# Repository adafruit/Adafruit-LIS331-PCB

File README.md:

## PCB files for the Adafruit LIS331 Family of High-g 3-Axis Accelerometers
### LIS331HH
<a href="http://www.adafruit.com/products/4626"><br/>
Click here to purchase one from the Adafruit shop</a>
### H3LIS331
<a href="http://www.adafruit.com/products/4627"><br/>
Click here to purchase one from the Adafruit shop</a>
### Links
PCB files for the Adafruit LIS331 Family of High-g 3-Axis Accelerometers. 

Format is EagleCAD schematic and board layout
* https://www.adafruit.com/product/4626
* https://www.adafruit.com/product/4627

### Description

Accelerometers are becoming fairly common, and their clear connection to movement makes them a particularly good choice for learning about sensors in a tangible way. It’s not hard to find an accelerometer that can measure accelerations up to 16g, but if you need an accelerometer that can measure even larger amounts of acceleration, your options narrow. The ICM20649 is a great sensor and can measure up to ±30g, but it also comes with a magnetometer that you may not need for your project.

Enter the LIS331 family of accelerometers from ST, including the H3LIS331 and LIS331HH. As their model numbers may suggest, the LIS331s are close cousins to the venerable LIS3DH accelerometer that is on every Circuit Playground, from the Circuit Playground Classic to the newest Circuit Playground Bluefruit. The LIS331s however can measure a wider range of acceleration values.

The LIS331HHis capable of measuring up to ±24g on each of its three axes for a total range of 48g! Should that not be enough for you the H3LIS331 will certainly have you covered. At the reasonable cost of some signal noise at lower “human level” accelerations, the H3’ can measure up to ±400g! The mind boggles at trying to think of what would need to measure that much acceleration. Perhaps you bought a surplus Sprint missile to start your own space program, or maybe you have an idea for a rocket sled based pizza delivery startup. The sky is the limit!

In addition to their substantial measurement capability, the LIS331s have built in and configurable high-pass and low-pass filters to adjust the readings to your application. Adjustable data rates also allow you to adjust how frequently to take measurements depending on your power budget, and SPI and I2C interfaces give them flexibility to allow them to be used in a range of applications.

The breakout for the  LIS331 family takes one of these little dynamos and puts it on a custom made PCB in the STEMMA QT form factor, making them easy to interface with. The STEMMA QT connectors on either side are compatible with the SparkFun Qwiic I2C connectors, allowing you to make solderless connections between your development board and the LIS331s, as well as being chained with a wide range of other sensors and accessories. We’ve of course broken out all the pins to standard headers and added a voltage regulator and level shifting so allow you to use it with either 3.3V or 5V systems such as the Metro M4 or Arduino Uno respectively.

Fancy as they are, breakouts alone won’t get you far, so we’ve written libraries for CircuitPython and Arduino along with example code to make them simple to use. The documentation for how to use the libraries as well as wiring diagrams on the following pages will show you how to use them to get you started.

### License

Adafruit invests time and resources providing this open source design, please support Adafruit and open-source hardware by purchasing products from [Adafruit](https://www.adafruit.com)!

Designed by Limor Fried/Ladyada for Adafruit Industries.

Creative Commons Attribution/Share-Alike, all text above must be included in any redistribution. 
See license.txt for additional details.

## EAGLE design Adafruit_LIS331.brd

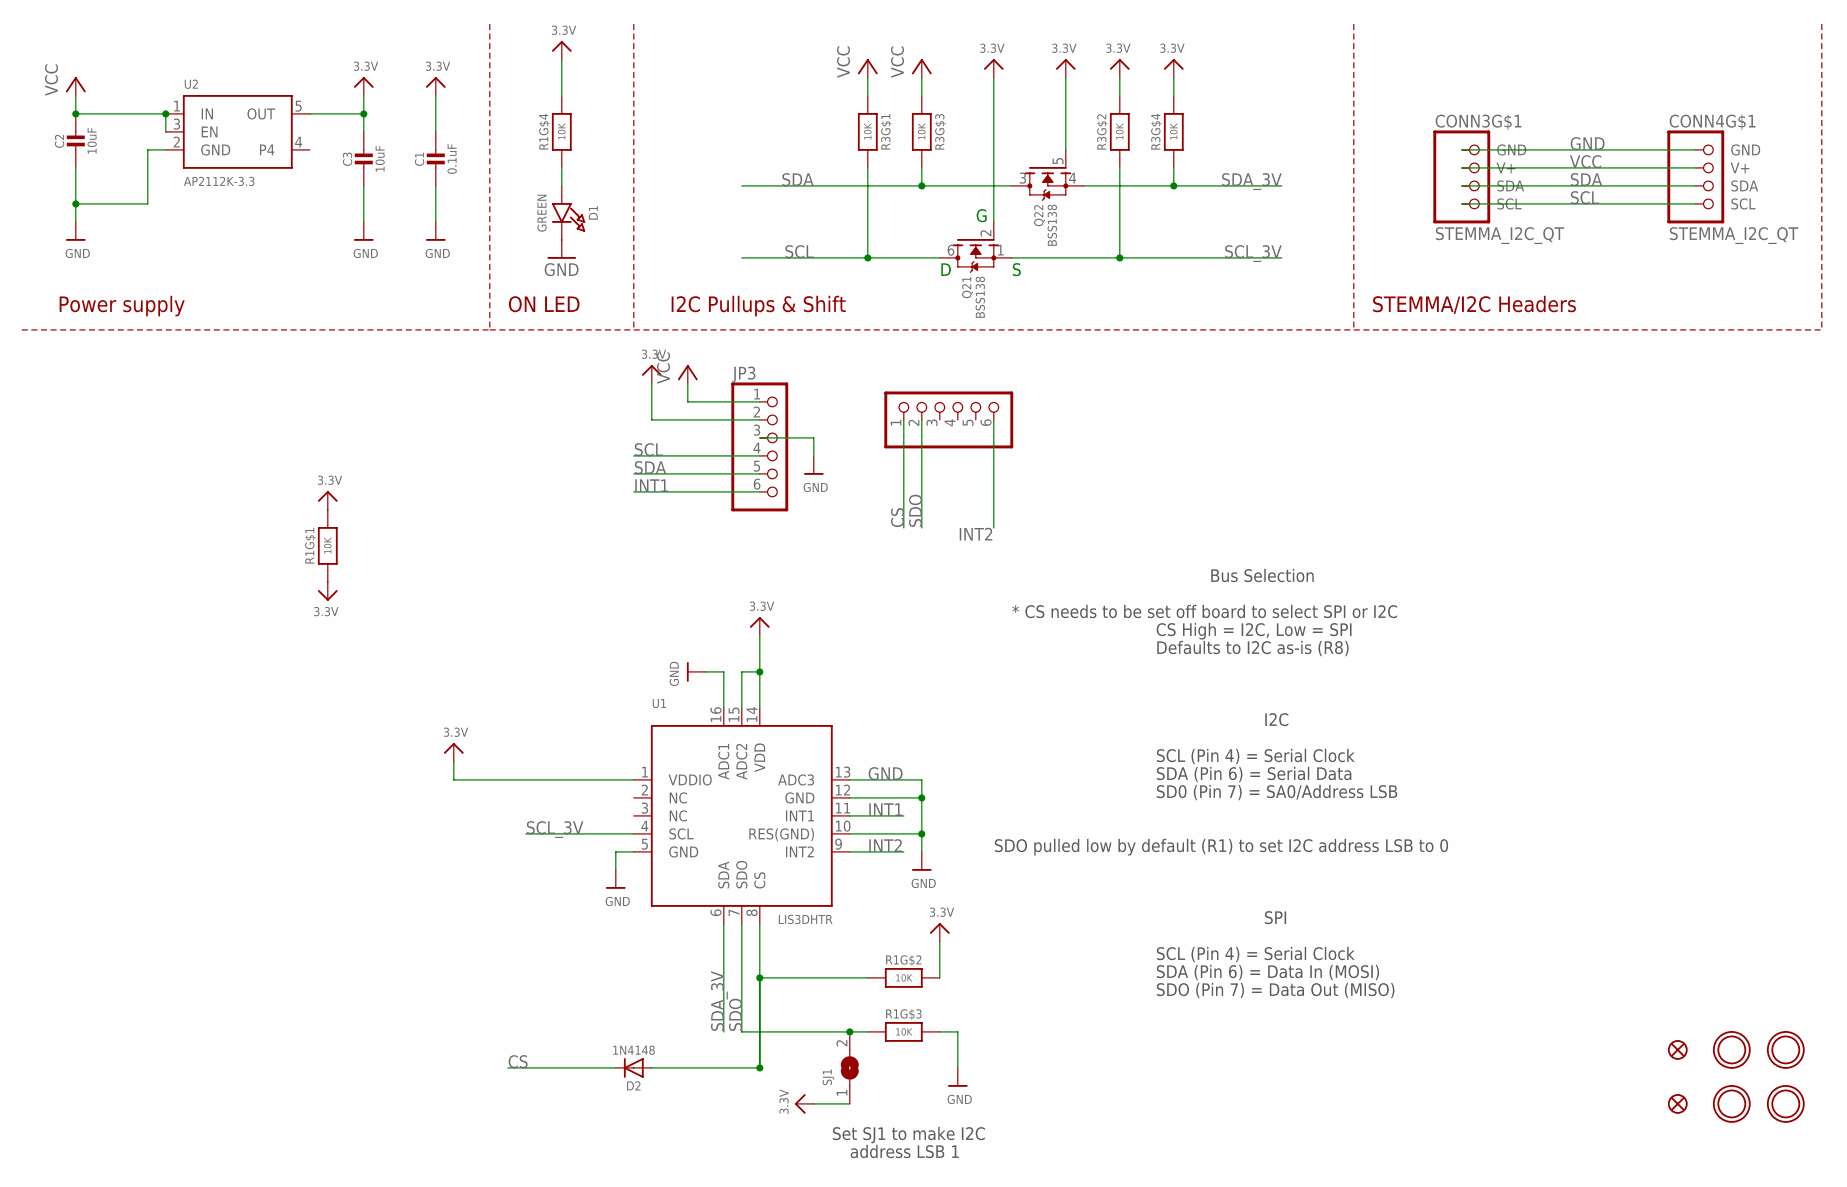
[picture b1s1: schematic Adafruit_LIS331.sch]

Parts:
C1: 0.1uF; 0603-NO
C2, C3: 10uF; 0805-NO
CONN3, CONN4: STEMMA_I2C_QT; JST_SH4
D1: GREEN; CHIPLED_0603_NOOUTLINE
D2: 1N4148; SOD-323
FID3, FID4: FIDUCIAL_1MM
JP2, JP3: HEADER-1X670MIL; 1X06_ROUND_70
Q2: BSS138; SOT363
R1, R3: 10K; RESPACK_4X0603
SJ1: SOLDERJUMPER; SOLDERJUMPER_ARROW_NOPASTE
U1: LIS3DHTR; LGA16_3X3MM
U2: AP2112K-3.3; SOT23-5
U$1, U$17, U$19, U$21: MOUNTINGHOLE2.5; MOUNTINGHOLE_2.5_PLATED

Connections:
3.3V: C1.1, C3.1, JP3.2, Q2.2 (G), Q2.5 (G), R1.1, R1.5 (2), R1.7 (2), R1.8 (2), R3.2 (1), R3.4 (1), SJ1.1, U1.1 (VDDIO), U1.14 (VDD), U1.15 (ADC2), U2.5 (OUT)
CS: D2.C, JP2.1
GND: C1.2, C2.2, C3.2, CONN3.1 (GND), CONN4.1 (GND), D1.C, JP3.3, R1.6 (2), U1.5 (GND), U1.10 (RES(GND)), U1.12 (GND), U1.13 (ADC3), U1.16 (ADC1), U2.2 (GND)
INT1: JP3.6, U1.11 (INT1)
INT2: JP2.6, U1.9 (INT2)
unnamed: D1.A, R1.4 (1)
unnamed: D2.A, R1.2 (1), U1.8 (CS)
SCL: CONN3.4 (SCL), CONN4.4 (SCL), JP3.4, Q2.6 (D), R3.8 (2)
SCL_3V: Q2.1 (S), R3.7 (2), U1.4 (SCL)
SDA: CONN3.3 (SDA), CONN4.3 (SDA), JP3.5, Q2.3 (D), R3.6 (2)
SDA_3V: Q2.4 (S), R3.5 (2), U1.6 (SDA)
SDO: JP2.2, R1.3 (1), SJ1.2, U1.7 (SDO)
VCC: C2.1, CONN3.2 (V+), CONN4.2 (V+), JP3.1, R3.1, R3.3 (1), U2.1 (IN), U2.3 (EN)

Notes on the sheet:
I2C Pullups & Shift
STEMMA/I2C Headers
ON LED
Power supply
I2C
SCL (Pin 4) = Serial Clock
SDA (Pin 6) = Serial Data
SD0 (Pin 7) = SA0/Address LSB
* CS needs to be set off board to select SPI or I2C
CS High = I2C, Low = SPI
Defaults to I2C as-is (R8)
SDO pulled low by default (R1) to set I2C address LSB to 0
Bus Selection
SPI
SDA (Pin 6) = Data In (MOSI)
SDO (Pin 7) = Data Out (MISO)
Set SJ1 to make I2C
address LSB 1

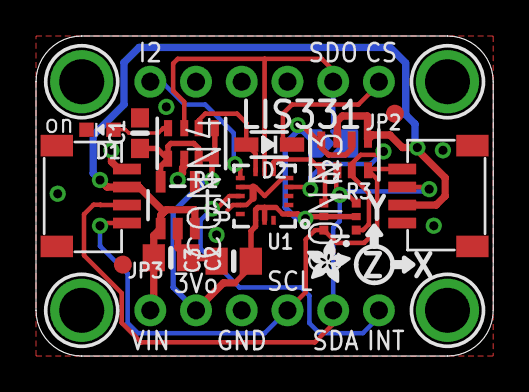
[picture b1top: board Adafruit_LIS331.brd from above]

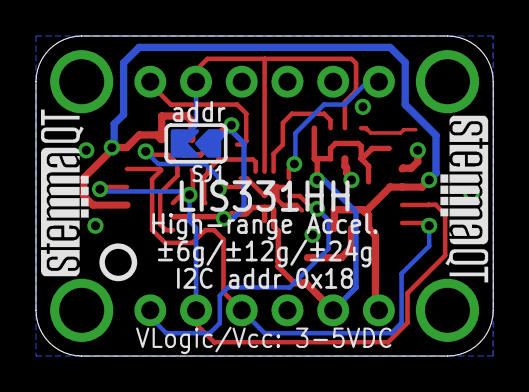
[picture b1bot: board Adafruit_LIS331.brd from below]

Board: 2 copper layers, 25.4 x 17.8 mm, 25 parts (4 on the bottom side), 13 nets.

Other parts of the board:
U$12: ADAFRUIT_2.5MM
U$25: PCBFEAT-REV-040
U$30, U$31: STEMMAQT

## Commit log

2020-05-14 Initial Commit of Rev B

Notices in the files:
parts and their libraries:
microbuilder: This work is placed in the public domain, and may be freely used for commercial and non-commercial work with the following conditions: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
